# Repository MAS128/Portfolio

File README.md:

# Welcome to My Professional Portfolio! 👋

Hi, I'm Marek, a versatile professional with expertise in **Data Analysis, Python Software Development, Data Science, CAD 3D Modeling, Embedded Systems, and PLC Programming**. This portfolio showcases my projects, skills, and contributions across these diverse fields.

---

## 🚀 **What I Do**

- **📊 Data Analysis**: Transforming raw data into actionable insights using Python, SQL, and data visualization tools like Tableau and Power BI.
- **🐍 Python Software Projects**: Building scalable and efficient applications, scripts, and automation tools.
- **🤖 Data Science**: Experimental work involving machine learning, data generation, augmentation and nerual network training.
- **🖥️ CAD 3D Modeling for 3D Printing**: Designing functional and creative 3D models using FreeCAD.
- **⚙️ Embedded Software Development**: Developing firmware and software for microcontrollers (e.g. ESP32, Arduino).
- **🔧 PLC Software**: Designing and programming PLC systems for industrial automation and control.

---

## 🛠️ **Skills & Tools**

### **Data Analysis**
- Python (Pandas, NumPy)
- SQL (mainly PostgreSQL & SQLite)
- Data Visualization (Plotly, Matplotlib, Dash, Seaborn, MS Excel)
- Machine Learning (Scikit-learn, TensorFlow)

### **Python Software Development**
- Python Frameworks (Flask, Django)
- Tools (Docker, VMs, VPNs, LLMs)
- APIs (REST, psycopg)
- Version Control (Git, GitHub)

### **Data Science**
- Jupyter Notebooks with TensorFlow
- Venvs with various ML and data visualisation libraries
- Custom Neural network models (simple, deep, residual, GRU)
- Experimental work ML and NN (Inverse Kinematics, Data Generation)

### **CAD 3D Modeling**
- FreeCAD
- Eagle (PCB Design)
- 3D Printing (Mainly Cura)

### **Embedded Software Development**
- C/C++ for Embedded Systems
- RTOS (FreeRTOS)
- Microcontrollers (ESP32, Arduino)

### **PLC Software**
- Ladder Logic, Structured Text
- Siemens TIA Portal
- Allen-Bradley Studio 5000
- SCADA Systems (WinCC)
- Simulation/Emulation Software (Demo 3D)

---

## 🌟 **Featured Projects**

### **1. Data Analysis: Employee Attrition Report**
- Data analysis project exploring the causes of worker attrition with the use of **IBM HR Analytics Employee Attrition & Performance** dataset
- Tools: Python, Seaborn, Pandas, Plotly.

### **2. Python Software Development: AI powered tagging application/agent**
- Fragment of a much larger system designed to periodically download social media posts from the external database, analyse them with locally hosted LLM, assign appropriate tags, then finally save the data back to the database for later use.
- Tools: Python, Docker, Django, Microservice Architecture, Microsoft Azure Cloud, Redis, PostgreSQL, RabbitMQ.

### **3. Embedded Software Development, CAD 3D Modeling + PCB Design: Gripper With Color Sensing**
- Desing and practical implementation of a mechanical gripper, operated by a microcontroller for a gantry crane model, as part of my Engineering degree.
- Tools: Arduino IDE, FreeCAD, Eagle (PCB Design)

### **4. Data Science: Neural Networks and Inverse Kinematics**
- Fragment of my Master thesis, where i explore direct usage of neural networks to solve inverse kinematics problem with self-supervised learning technique.
- Tools: Python, Jupyter-lab, TensorFlow, Mathematical Modeling, Plotly, Clustering techniques, Deep Neural Networks

---

## 📂 **Explore My Work**
Check out my projects in their respective subdirectories.

---

## 📫 **Let’s Connect!**
I’m always open to collaboration, new opportunities, or freelance work. Feel free to reach out:

- **Email**: [m.sarnecki99@gmail.com]
- **LinkedIn**: [Marek Sarnecki](https://www.linkedin.com/in/marek-sarnecki-057846344/)

---

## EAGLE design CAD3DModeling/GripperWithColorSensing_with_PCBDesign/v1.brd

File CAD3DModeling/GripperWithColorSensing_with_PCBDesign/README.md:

# Servo-Based Gripping Mechanism with Light Sensor Control, CAD, and PCB Design

## Overview: CAD Design

The gripper features a worm gear coupled with a servo mechanism, converting rotational torque into a synchronised gripping action via four geared arms. A worm gear was chosen for its self-locking properties, ensuring that when the servo loses power, the gripper remains locked in place.

The parts were specifically designed and optimised for 3D printing, allowing for efficient fabrication. The entire mechanism is assembled using four screws, though some components require superglue to secure the servo mount properly.

## Overview: PCB Design

The PCB is built around an AVR microcontroller, specifically an Arduino Nano (off-brand AVR to reduce costs). It includes:

- Expansion pins for future modifications.
- LED indicators to display the microcontroller’s status.
- Manual operation buttons for direct control.
- An opto-electronic couplers for secure signal exchange with a higher voltage system.

The board supports 5V and 12V power lines, along with high-current traces for driving the servo.

---

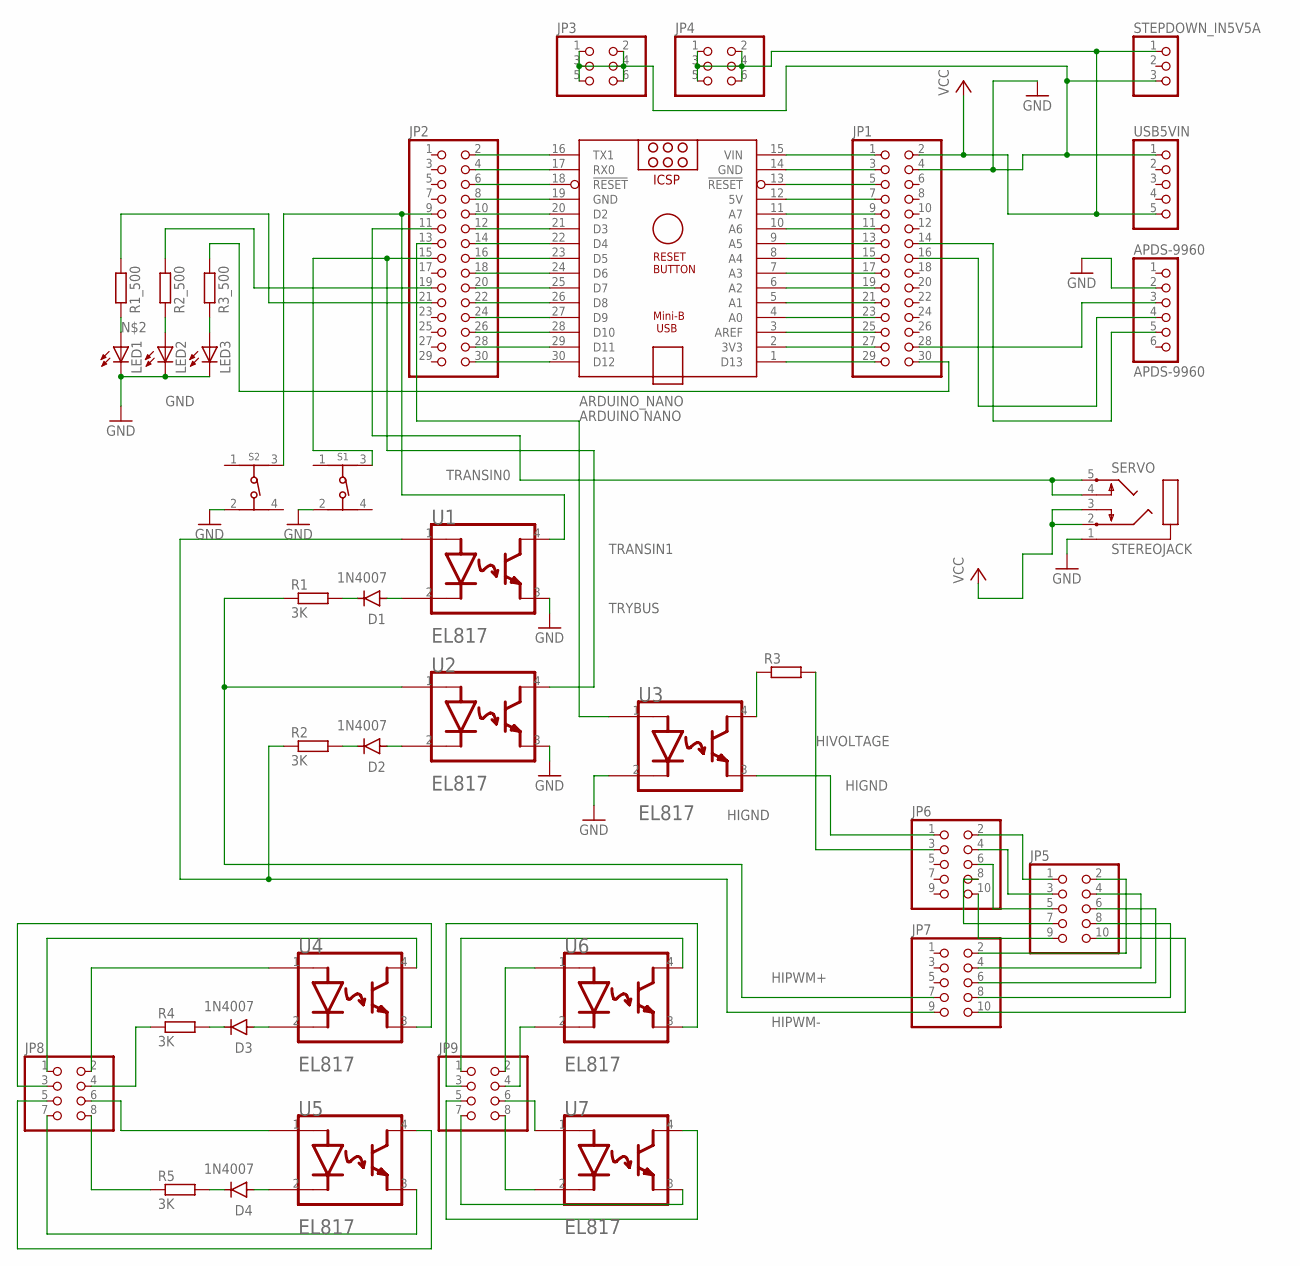
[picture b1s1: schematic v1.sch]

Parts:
APDS-9960: APDS-9960; 1X06
ARDUINO_NANO: ARDUINO NANO; ARDUINO_NANO
D1, D2, D3, D4: 1N4007; DO-41
JP1, JP2: PINHD-2X15; 2X15
JP3, JP4: PINHD-2X3; 2X03
JP5, JP6, JP7: PINHD-2X5; 2X05
JP8, JP9: PINHD-2X4; 2X04
LED1, LED2, LED3: LED3MM
R1, R2, R4, R5: 3K; 0207/10
R1_500, R2_500, R3, R3_500: R-EU_0207/10; 0207/10
S1, S2: 430156070726; 4301X60707X6
SERVO: STEREOJACK; STX3100
STEPDOWN_IN5V5A: PINHD-1X3; 1X03
U1, U2, U3, U4, U5, U6, U7: EVERLIGHT_EL817EVERLIGHT_EL817_0_0; EVERLIGHT_EL817_0
USB5VIN: PINHD-1X5; 1X05

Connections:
3V3: APDS-9960.3, JP1.28
D13: JP1.30, R3_500.1
GND: APDS-9960.2, JP1.4, JP3.1, JP3.2, JP3.3, JP3.4, JP3.5, JP3.6, LED1.K (C), LED2.K (C), LED3.K (C), S1.2, S2.2, SERVO.1, STEPDOWN_IN5V5A.3, U1.3 (EMITTER), U2.3 (EMITTER), U3.2 (CATHODE), USB5VIN.1
HIGND: JP6.1, U3.3 (EMITTER)
HIPWM+: JP7.7, R1.1, U2.1 (ANODE)
HIPWM-: JP7.9, R2.1, U1.1 (ANODE)
HIPWM-1: JP8.4, R4.1
HIPWM-2: JP8.8, R5.1
HIVOLTAGE: JP6.3, R3.2
LEDCLOSE: JP2.19, R2_500.1
LEDSENSOR: JP2.21, R1_500.1
unnamed: LED1.A, R1_500.2
unnamed: LED2.A, R2_500.2
unnamed: LED3.A, R3_500.2
unnamed: D3.A, U4.2 (CATHODE)
unnamed: D1.A, U1.2 (CATHODE)
unnamed: D2.A, U2.2 (CATHODE)
unnamed: D1.C, R1.2
unnamed: D2.C, R2.2
unnamed: D3.C, R4.2
unnamed: D4.A, U5.2 (CATHODE)
unnamed: D4.C, R5.2
unnamed: ARDUINO_NANO.8 (A4), JP1.15
unnamed: JP5.1, JP6.2
unnamed: ARDUINO_NANO.13 (!RESET), JP1.5
unnamed: ARDUINO_NANO.12 (5V), JP1.7
unnamed: ARDUINO_NANO.11 (A7), JP1.9
unnamed: ARDUINO_NANO.10 (A6), JP1.11
unnamed: ARDUINO_NANO.2 (3V3), JP1.27
unnamed: ARDUINO_NANO.9 (A5), JP1.13
unnamed: ARDUINO_NANO.7 (A3), JP1.17
unnamed: ARDUINO_NANO.6 (A2), JP1.19
unnamed: ARDUINO_NANO.5 (A1), JP1.21
unnamed: ARDUINO_NANO.4 (A0), JP1.23
unnamed: ARDUINO_NANO.3 (AREF), JP1.25
unnamed: ARDUINO_NANO.15 (VIN), JP1.1
unnamed: ARDUINO_NANO.1 (D13), JP1.29
unnamed: ARDUINO_NANO.16 (TX1), JP2.2
unnamed: ARDUINO_NANO.17 (RX0), JP2.4
unnamed: ARDUINO_NANO.18 (!RESET), JP2.6
unnamed: ARDUINO_NANO.19 (GND), JP2.8
unnamed: ARDUINO_NANO.20 (D2), JP2.10
unnamed: ARDUINO_NANO.14 (GND), JP1.3
unnamed: ARDUINO_NANO.22 (D4), JP2.14
unnamed: ARDUINO_NANO.23 (D5), JP2.16
unnamed: ARDUINO_NANO.24 (D6), JP2.18
unnamed: ARDUINO_NANO.25 (D7), JP2.20
unnamed: ARDUINO_NANO.26 (D8), JP2.22
unnamed: ARDUINO_NANO.27 (D9), JP2.24
unnamed: ARDUINO_NANO.28 (D10), JP2.26
unnamed: ARDUINO_NANO.29 (D11), JP2.28
unnamed: ARDUINO_NANO.30 (D12), JP2.30
unnamed: JP5.3, JP6.4
unnamed: JP5.5, JP6.6
unnamed: ARDUINO_NANO.21 (D3), JP2.12
unnamed: JP5.7, JP6.8
unnamed: JP5.9, JP6.10
unnamed: JP5.2, JP7.2
unnamed: JP5.4, JP7.4
unnamed: JP5.6, JP7.6
unnamed: JP5.8, JP7.8
unnamed: JP5.10, JP7.10
unnamed: JP8.2, U4.1 (ANODE)
unnamed: JP8.6, U5.1 (ANODE)
unnamed: JP8.1, U4.4 (COLLECTOR)
unnamed: R3.1, U3.4 (COLLECTOR)
unnamed: JP8.3, U4.3 (EMITTER)
unnamed: JP8.7, U5.3 (EMITTER)
unnamed: JP8.5, U5.4 (COLLECTOR)
unnamed: JP9.2, U6.1 (ANODE)
unnamed: JP9.4, U6.2 (CATHODE)
unnamed: JP9.6, U7.1 (ANODE)
unnamed: JP9.8, U7.2 (CATHODE)
unnamed: JP9.1, U6.4 (COLLECTOR)
unnamed: JP9.3, U6.3 (EMITTER)
unnamed: JP9.7, U7.3 (EMITTER)
unnamed: JP9.5, U7.4 (COLLECTOR)
SCL: APDS-9960.5, JP1.14
SDA: APDS-9960.4, JP1.16
SERVO: JP2.11, SERVO.4, SERVO.5
TRANSIN0: JP2.9, S2.3, U1.4 (COLLECTOR)
TRANSIN1: JP2.15, S1.3, U2.4 (COLLECTOR)
TRYBUS: JP2.13, U3.1 (ANODE)
VCC: JP1.2, JP4.1, JP4.2, JP4.3, JP4.4, JP4.5, JP4.6, SERVO.2, SERVO.3, STEPDOWN_IN5V5A.1, USB5VIN.5

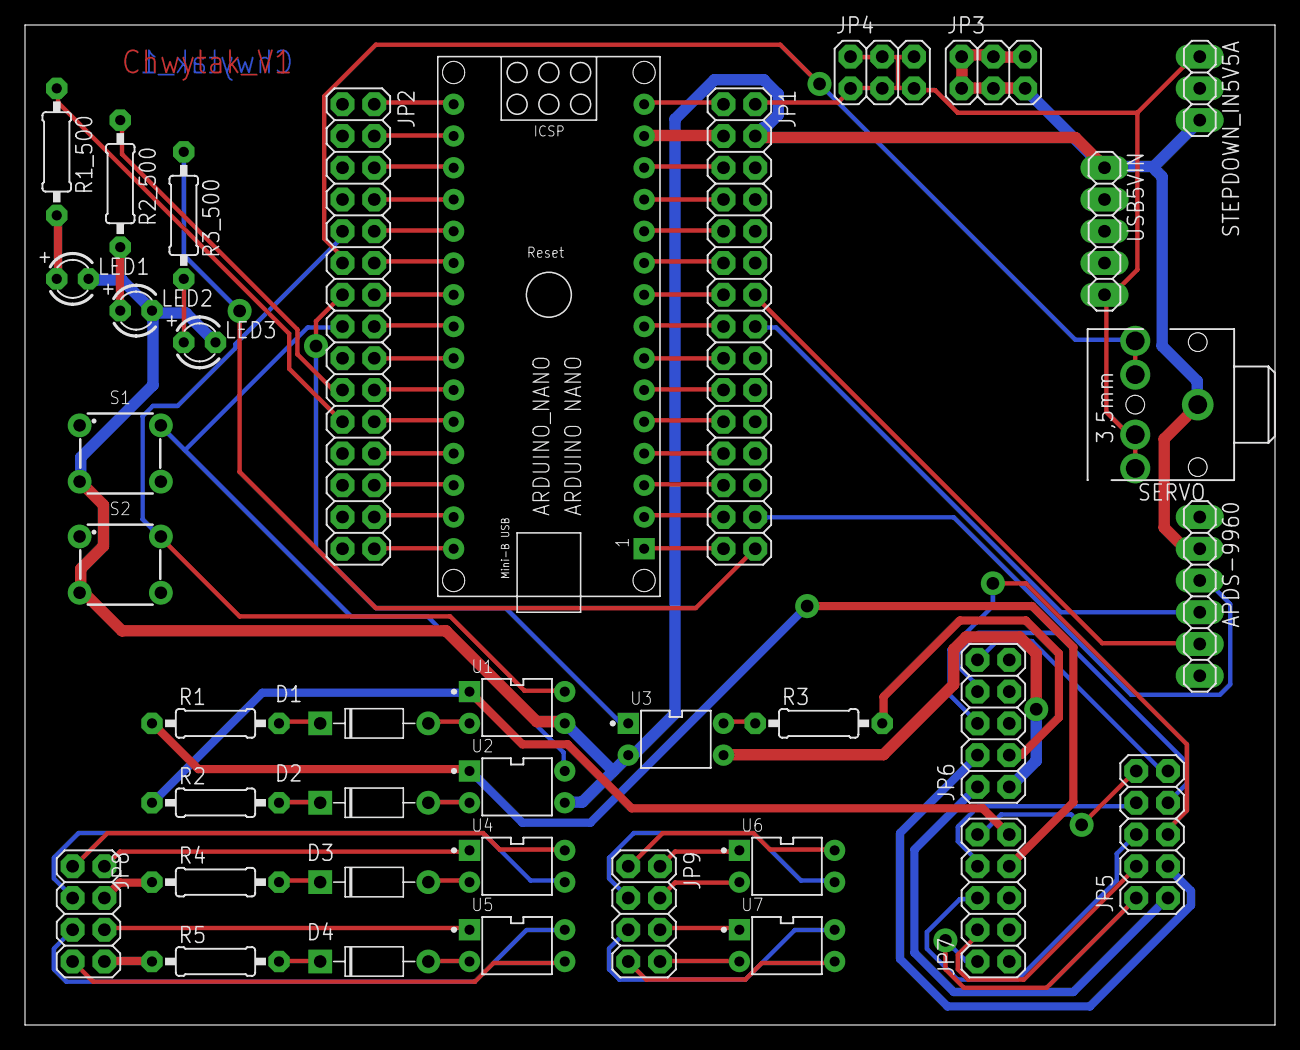
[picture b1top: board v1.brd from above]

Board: 2 copper layers, 100.0 x 80.0 mm, 38 parts (0 on the bottom side), 84 nets.

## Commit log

2025-02-02 Create README.md
    initial portfolio description
2025-02-02 project init
2025-02-02 Added description for the DA project
2025-02-02 Started EDA, looking for significant factors causing work attrition
2025-02-03 Added anonimised code that was used in the much larger system when i was working at a startup.
2025-02-03 Updated .md file
2025-02-03 Refined .md file
2025-02-03 added project desription
2025-02-03 Added embedded software project
2025-02-03 added descriptions and fixes
2025-02-03 added descriptions and images
2025-02-03 fixes
2025-02-03 added visualisation
2025-02-05 Added code and research notebooks for my masters degree project
2025-02-05 Added description
2025-02-05 updated main readme file
2025-02-25 Remove .DS_Store files
2025-02-25 fix 2
2025-02-25 fix 3

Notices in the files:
parts and their libraries:
Wurth_Switch_WS-TATV: Copyright: Würth Elektronik
